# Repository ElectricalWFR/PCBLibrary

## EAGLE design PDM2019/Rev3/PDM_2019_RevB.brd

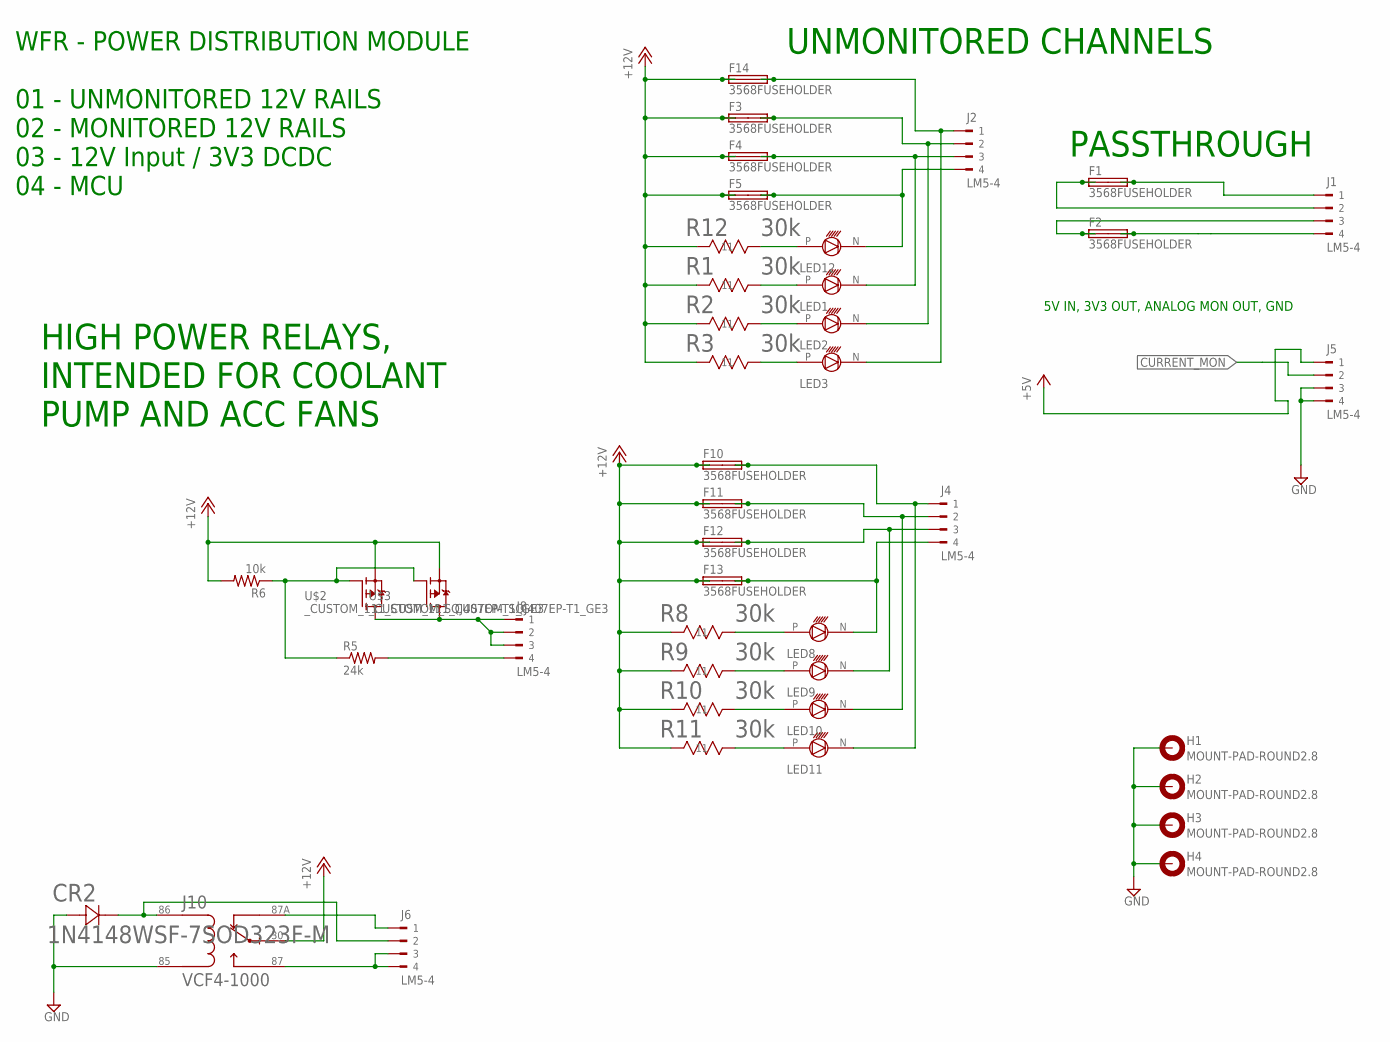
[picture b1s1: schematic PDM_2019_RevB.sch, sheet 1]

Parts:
CR2: 1N4148WSF-7SOD323F-M; SOD323F-M
F1, F2, F3, F4, F5, F10, F11, F12, F13, F14: 3568FUSEHOLDER; 3568
H1, H2, H3, H4: MOUNT-PAD-ROUND2.8; 2,8-PAD
J1, J2, J4, J5, J6, J8: LM5-4; 281-1423
J10: VCF4-1000; TE_VCF4-1000
LED1, LED2, LED3, LED8, LED9, LED10, LED11, LED12: 5MM_LED
R1, R2, R3, R8, R9, R10, R11, R12: 30k; STA_RMCF0805
R5: 24k; M0805
R6: 10k; M0805
U$2, U$3: _CUSTOM_111_CUSTOM_SQJ407EP-T1_GE3; _CUSTOM_111_CUSTOM_TRANS_SIRA90DP-T1-GE3

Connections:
+5V: J5.P$1 (1); also elsewhere on the board
+12V: F3.L1 (1A), F3.L2 (1B), F4.L1 (1A), F4.L2 (1B), F5.L1 (1A), F5.L2 (1B), F10.L1 (1A), F10.L2 (1B), F11.L1 (1A), F11.L2 (1B), F12.L1 (1A), F12.L2 (1B), F13.L1 (1A), F13.L2 (1B), F14.L1 (1A), F14.L2 (1B), J10.30, R1.1 (11), R2.1 (11), R3.1 (11), R6.2, R8.1 (11), R9.1 (11), R10.1 (11), R11.1 (11), R12.1 (11), U$2.1 (S), U$2.2 (S), U$2.3 (S), U$3.1 (S), U$3.2 (S), U$3.3 (S); also elsewhere on the board
CURRENT_MON: J5.P$2 (2); also elsewhere on the board
GND: CR2.2 (21), H1.B2,8, H2.B2,8, H3.B2,8, H4.B2,8, J5.P$3 (3), J5.P$4 (4), J10.85; also elsewhere on the board
unnamed: F1.R1 (2A), F1.R2 (2B), J1.P$1 (1)
unnamed: F1.L1 (1A), F1.L2 (1B), J1.P$2 (2)
unnamed: F2.L1 (1A), F2.L2 (1B), J1.P$3 (3)
unnamed: LED11.P, R11.2 (22)
unnamed: LED12.P, R12.2 (22)
unnamed: F4.R1 (2A), F4.R2 (2B), J2.P$3 (3), LED1.N
unnamed: F5.R1 (2A), F5.R2 (2B), J2.P$4 (4), LED12.N
unnamed: J8.P$4 (4), R5.2
unnamed: J8.P$1 (1), J8.P$2 (2), J8.P$3 (3), U$2.5 (D), U$3.5 (D)
unnamed: F10.R1 (2A), F10.R2 (2B), J4.P$1 (1), LED11.N
unnamed: F13.R1 (2A), F13.R2 (2B), J4.P$4 (4), LED8.N
unnamed: F12.R1 (2A), F12.R2 (2B), J4.P$3 (3), LED9.N
unnamed: F11.R1 (2A), F11.R2 (2B), J4.P$2 (2), LED10.N
unnamed: R5.1, R6.1, U$2.4 (G), U$3.4 (G)
unnamed: LED10.P, R10.2 (22)
unnamed: LED8.P, R8.2 (22)
unnamed: CR2.1 (12), J6.P$2 (2), J10.86
unnamed: LED9.P, R9.2 (22)
unnamed: F2.R1 (2A), F2.R2 (2B), J1.P$4 (4)
unnamed: LED1.P, R1.2 (22)
unnamed: LED2.P, R2.2 (22)
unnamed: LED3.P, R3.2 (22)
unnamed: F3.R1 (2A), F3.R2 (2B), J2.P$2 (2), LED2.N
unnamed: F14.R1 (2A), F14.R2 (2B), J2.P$1 (1), LED3.N
unnamed: J6.P$3 (3), J6.P$4 (4), J10.87
unnamed: J6.P$1 (1), J10.87A

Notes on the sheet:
WFR - POWER DISTRIBUTION MODULE 01 - UNMONITORED 12V RAILS 02 - MONITORED 12V RAILS 03 - 12V Input / 3V3 DCDC 04 - MCU
HIGH POWER RELAYS, INTENDED FOR COOLANT PUMP AND ACC FANS
UNMONITORED CHANNELS
PASSTHROUGH
5V IN, 3V3 OUT, ANALOG MON OUT, GND

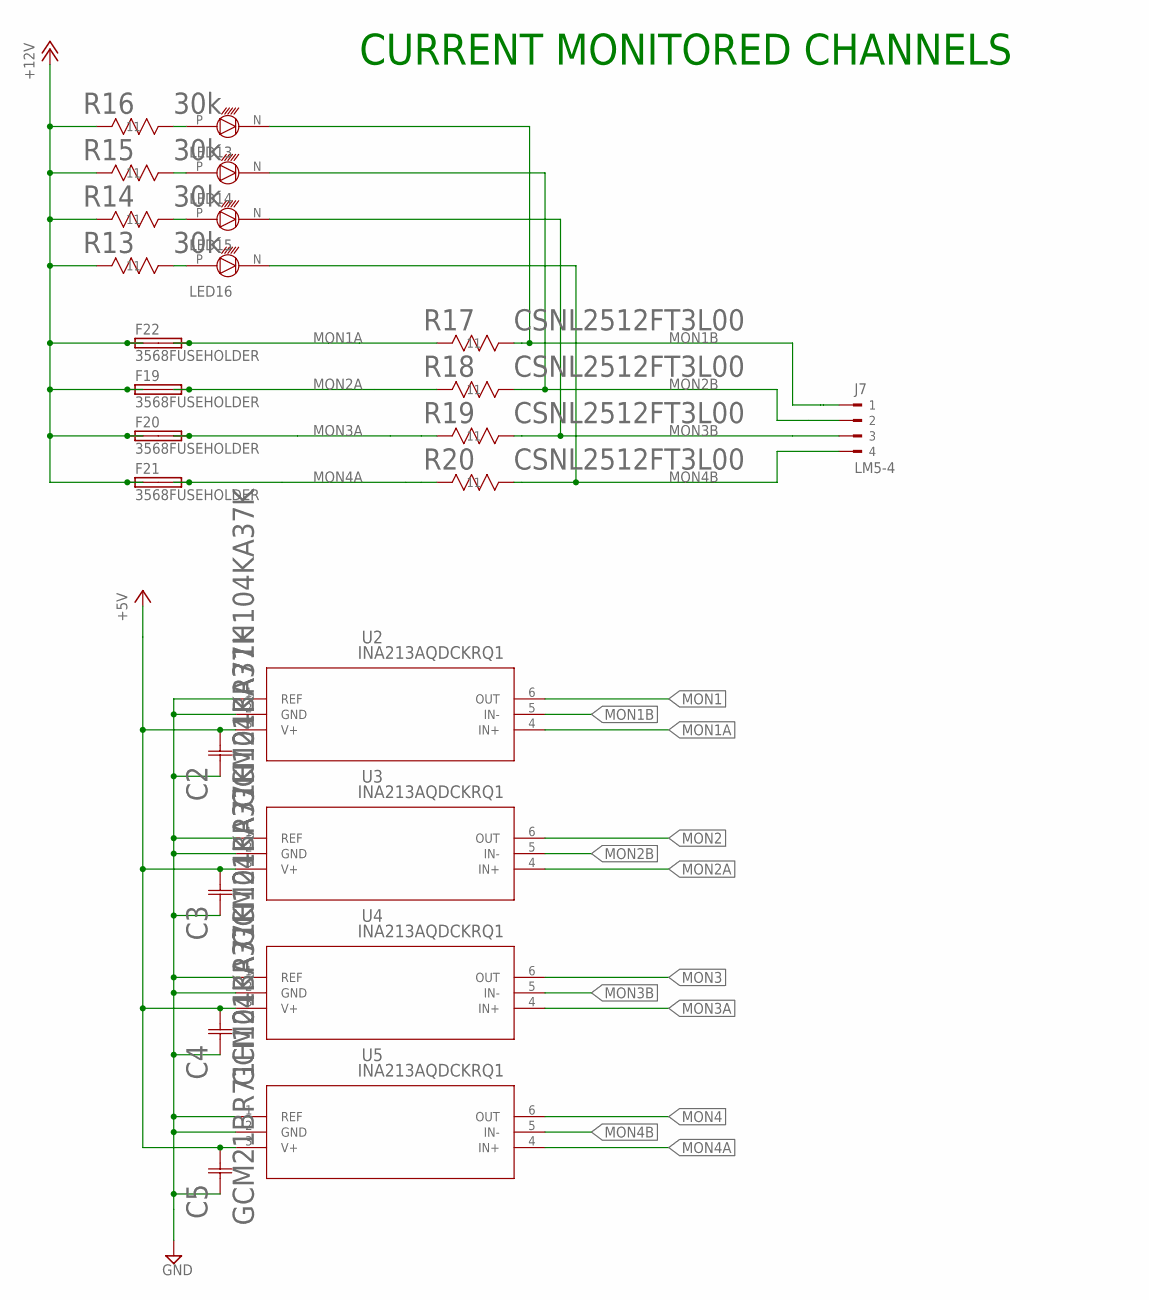
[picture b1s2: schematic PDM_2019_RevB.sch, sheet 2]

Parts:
C2, C3, C4, C5: GCM21BR71H104KA37K; G-21
F19, F20, F21, F22: 3568FUSEHOLDER; 3568
J7: LM5-4; 281-1423
LED13, LED14, LED15, LED16: 5MM_LED
R13, R14, R15, R16: 30k; STA_RMCF0805
R17, R18, R19, R20: CSNL2512FT3L00; STA_CSNL2512(3)
U2, U3, U4, U5: INA213AQDCKRQ1; DCK6

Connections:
+5V: C2.2 (22), C3.2 (22), C4.2 (22), C5.2 (22), U2.3 (V+), U3.3 (V+), U4.3 (V+), U5.3 (V+); also elsewhere on the board
+12V: F19.L1 (1A), F19.L2 (1B), F20.L1 (1A), F20.L2 (1B), F21.L1 (1A), F21.L2 (1B), F22.L1 (1A), F22.L2 (1B), R13.1 (11), R14.1 (11), R15.1 (11), R16.1 (11); also elsewhere on the board
GND: C2.1 (11), C3.1 (11), C4.1 (11), C5.1 (11), U2.1 (REF), U2.2 (GND), U3.1 (REF), U3.2 (GND), U4.1 (REF), U4.2 (GND), U5.1 (REF), U5.2 (GND); also elsewhere on the board
MON1: U2.6 (OUT); also elsewhere on the board
MON1A: F22.R1 (2A), F22.R2 (2B), R17.1 (11), U2.4 (IN+)
MON1B: J7.P$1 (1), LED13.N, R17.2 (22), U2.5 (IN-)
MON2: U3.6 (OUT); also elsewhere on the board
MON2A: F19.R1 (2A), F19.R2 (2B), R18.1 (11), U3.4 (IN+)
MON2B: J7.P$2 (2), LED14.N, R18.2 (22), U3.5 (IN-)
MON3: U4.6 (OUT); also elsewhere on the board
MON3A: F20.R1 (2A), F20.R2 (2B), R19.1 (11), U4.4 (IN+)
MON3B: J7.P$3 (3), LED15.N, R19.2 (22), U4.5 (IN-)
MON4: U5.6 (OUT); also elsewhere on the board
MON4A: F21.R1 (2A), F21.R2 (2B), R20.1 (11), U5.4 (IN+)
MON4B: J7.P$4 (4), LED16.N, R20.2 (22), U5.5 (IN-)
unnamed: LED16.P, R13.2 (22)
unnamed: LED15.P, R14.2 (22)
unnamed: LED14.P, R15.2 (22)
unnamed: LED13.P, R16.2 (22)

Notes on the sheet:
CURRENT MONITORED CHANNELS

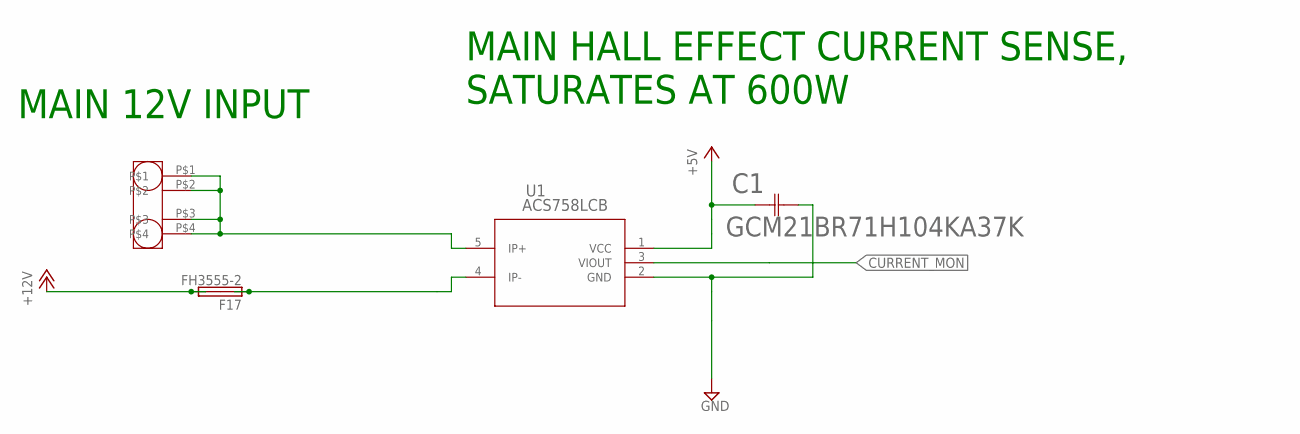
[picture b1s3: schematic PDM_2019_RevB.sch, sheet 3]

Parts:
C1: GCM21BR71H104KA37K; G-21
F17: FH3555-2; 3555-2
U1: ACS758LCB; PFF-5
U$1: 1773976

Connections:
+5V: C1.1 (11), U1.1 (VCC); also elsewhere on the board
+12V: F17.R1 (2A), F17.R2 (2B); also elsewhere on the board
CURRENT_MON: U1.3 (VIOUT); also elsewhere on the board
GND: C1.2 (22), U1.2 (GND); also elsewhere on the board
unnamed: U1.5 (IP+), U$1.P$1, U$1.P$2, U$1.P$3, U$1.P$4
unnamed: F17.L1 (1A), F17.L2 (1B), U1.4 (IP-)

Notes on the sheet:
MAIN 12V INPUT
MAIN HALL EFFECT CURRENT SENSE, SATURATES AT 600W

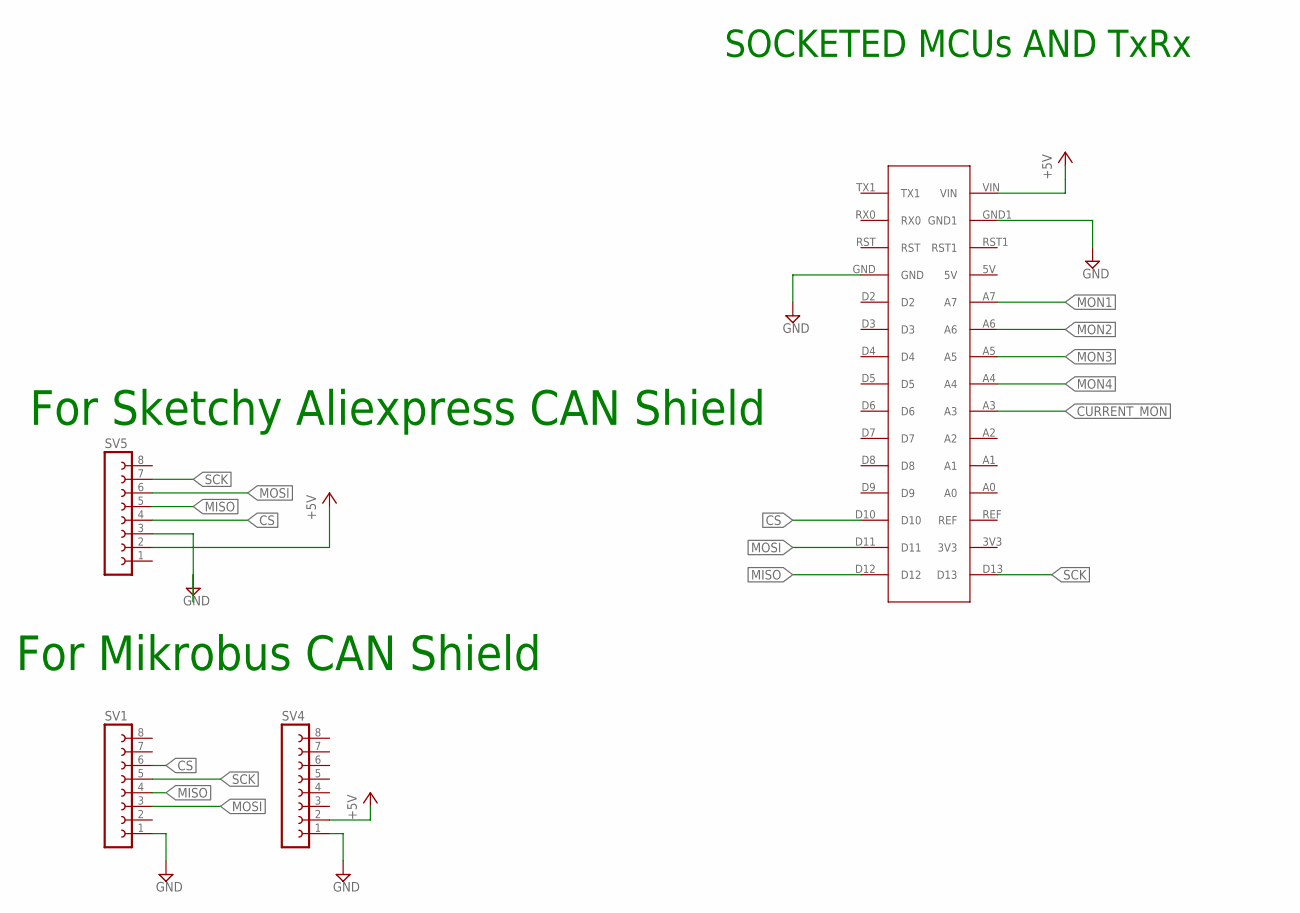
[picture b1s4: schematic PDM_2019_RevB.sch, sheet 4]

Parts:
SV1, SV4, SV5: FE08-1; FE08
U$4: NANO

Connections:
+5V: SV4.2; also elsewhere on the board
CS: SV1.6, SV5.4, U$4.D10
CURRENT_MON: U$4.A3; also elsewhere on the board
GND: SV1.1, SV4.1, U$4.GND, U$4.GND1; also elsewhere on the board
MISO: SV1.4, SV5.5, U$4.D12
MON1: U$4.A7; also elsewhere on the board
MON2: U$4.A6; also elsewhere on the board
MON3: U$4.A5; also elsewhere on the board
MON4: U$4.A4; also elsewhere on the board
MOSI: SV1.3, SV5.6, U$4.D11
SCK: SV1.5, SV5.7, U$4.D13

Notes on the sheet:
For Mikrobus CAN Shield
For Sketchy Aliexpress CAN Shield
SOCKETED MCUs AND TxRx

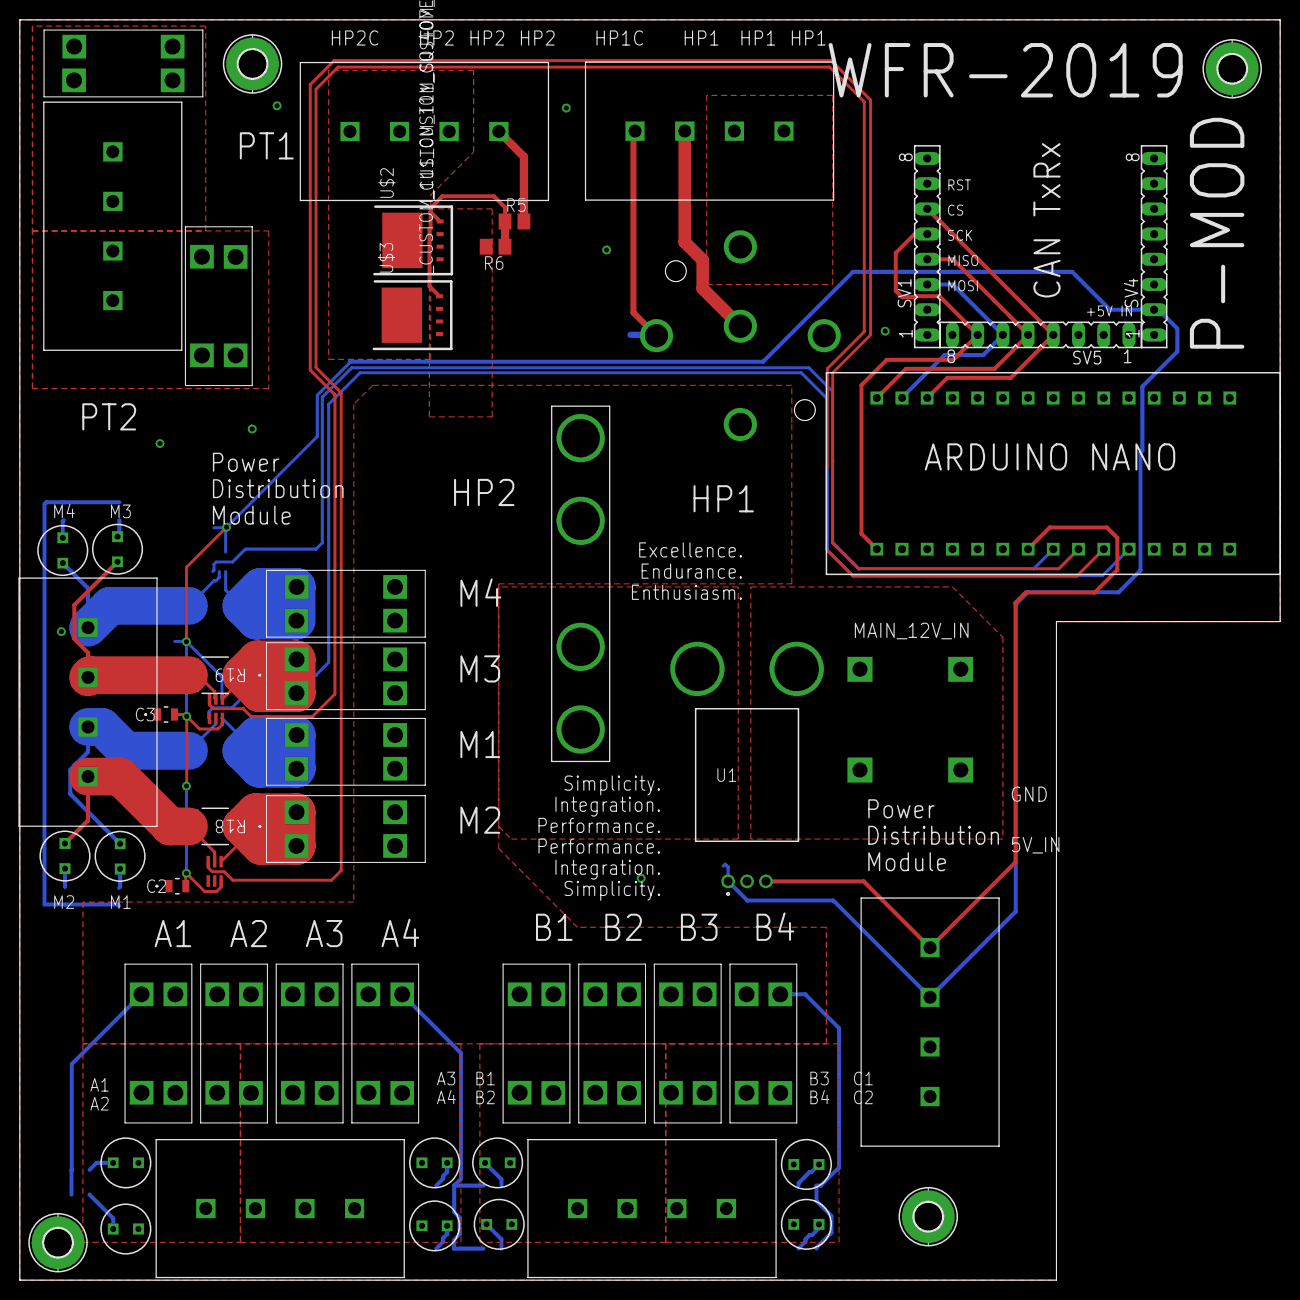
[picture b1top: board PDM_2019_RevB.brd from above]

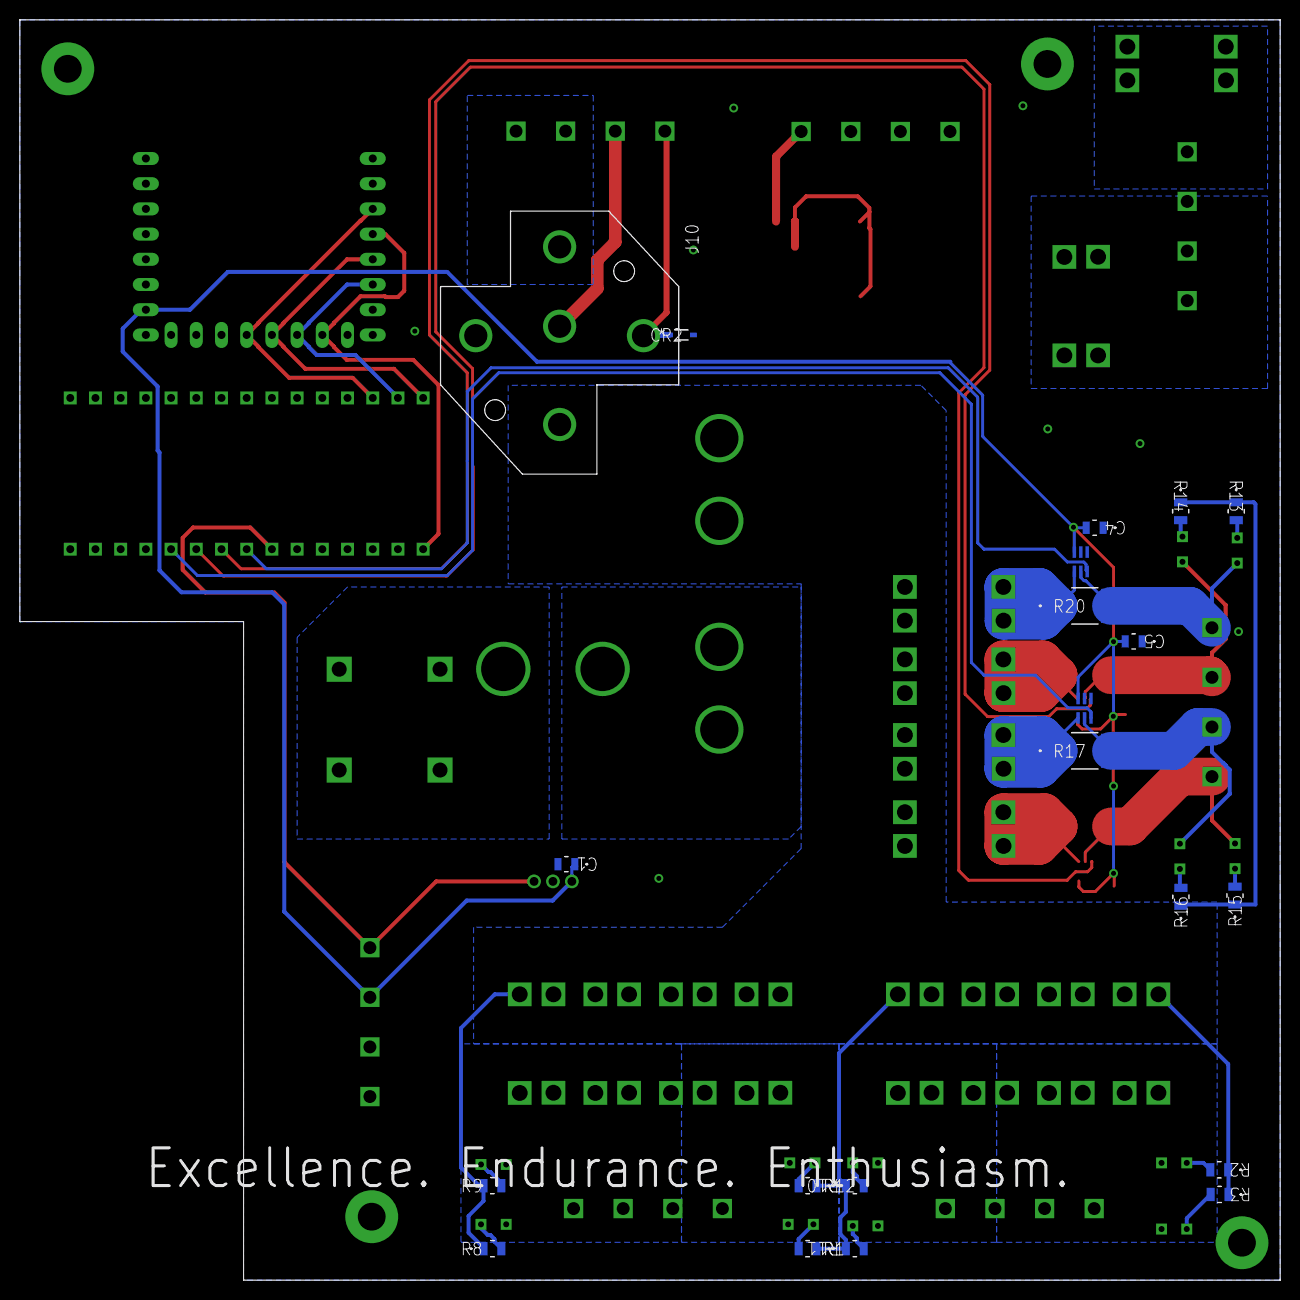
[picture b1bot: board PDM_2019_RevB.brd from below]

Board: 2 copper layers, 127.0 x 127.0 mm, 75 parts (21 on the bottom side), 52 nets.

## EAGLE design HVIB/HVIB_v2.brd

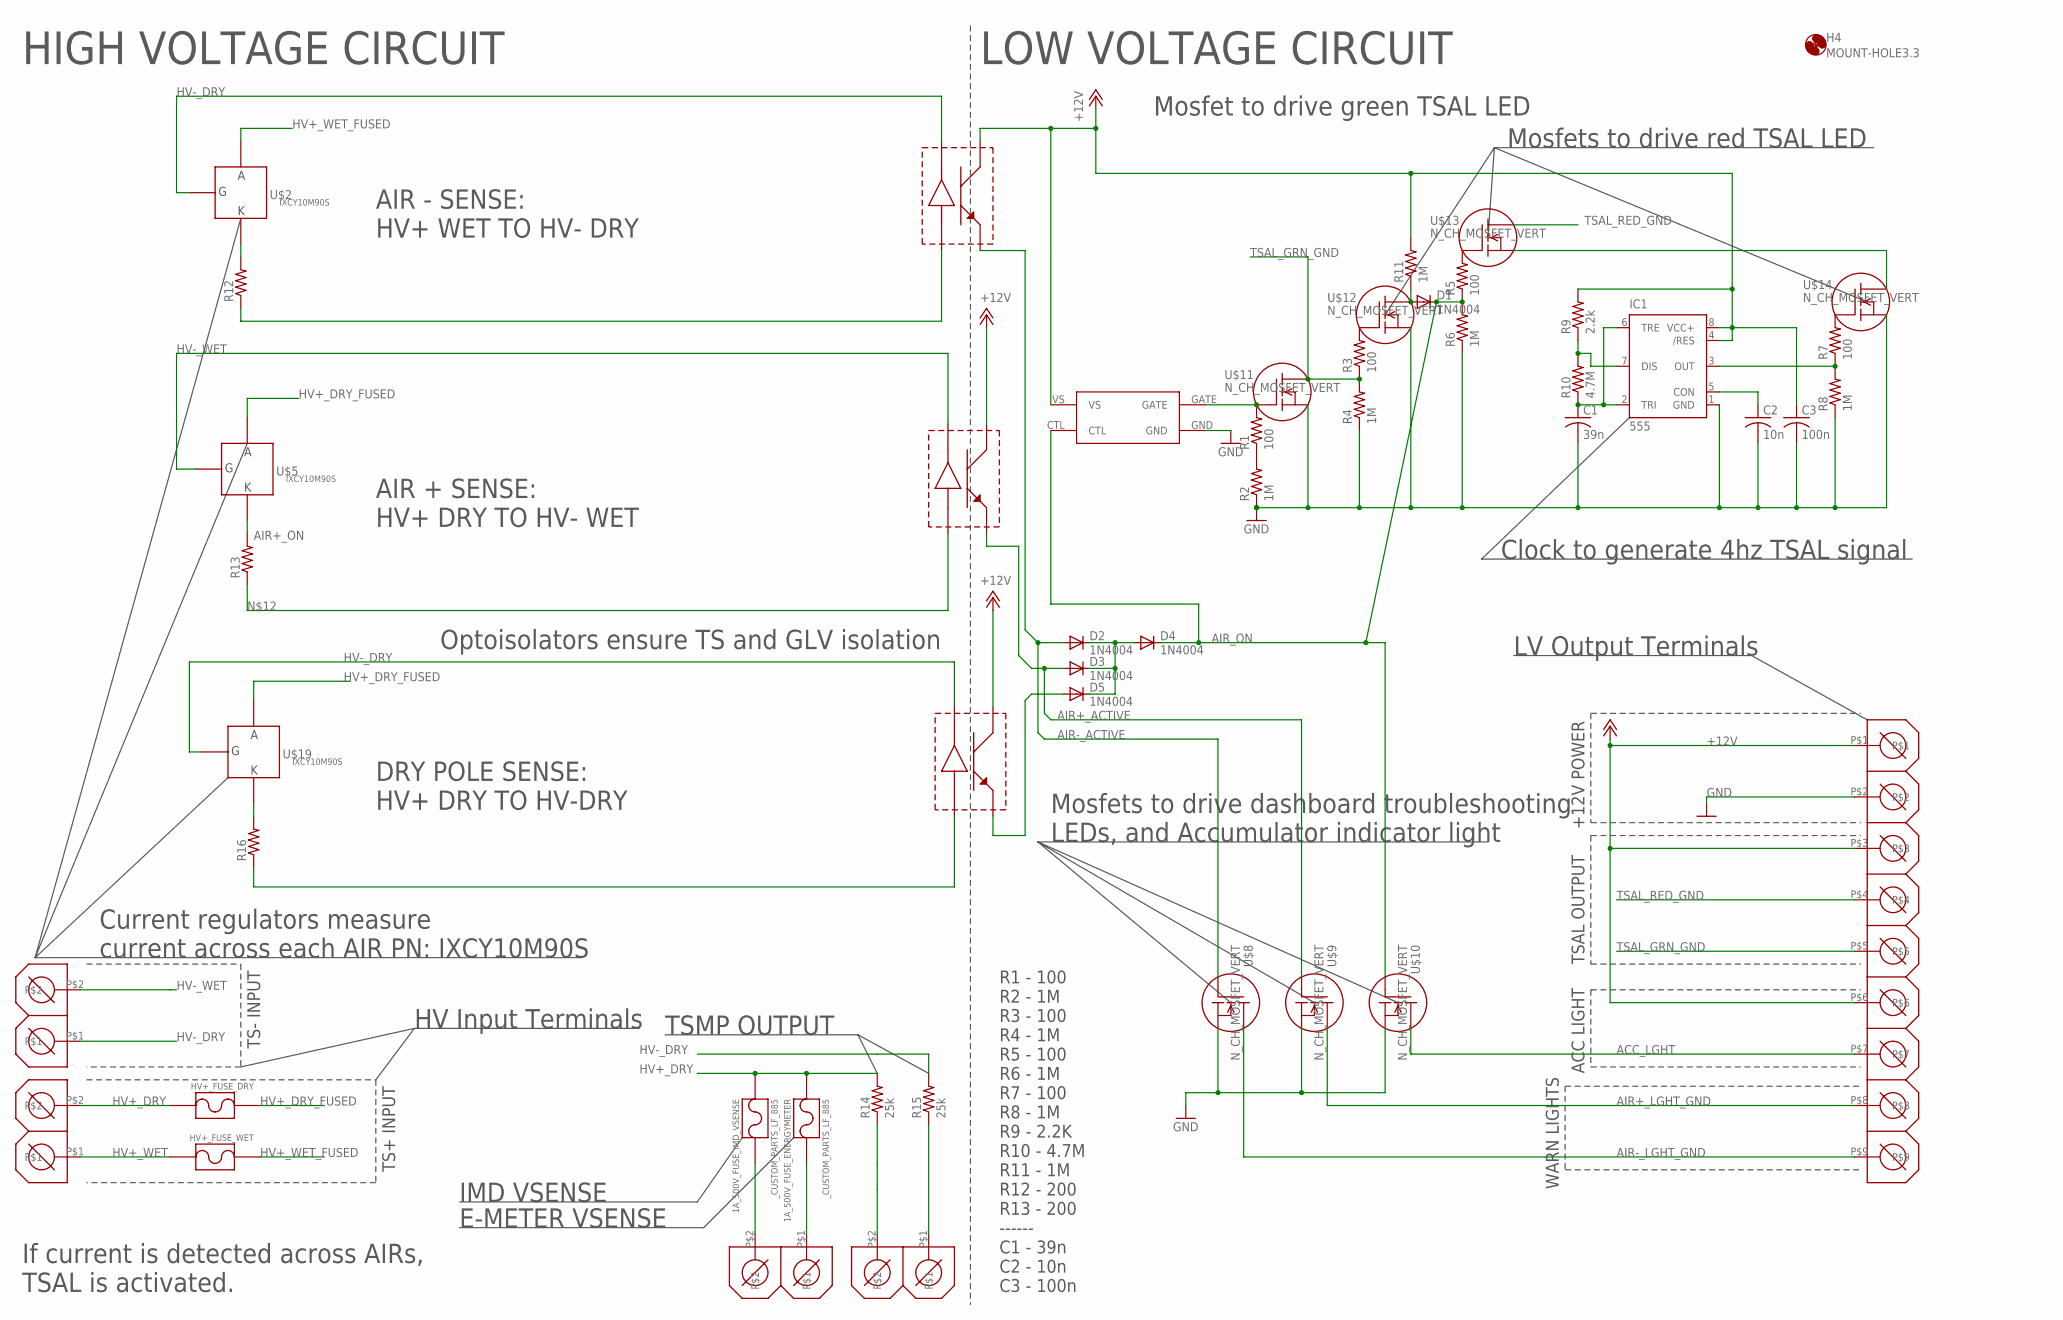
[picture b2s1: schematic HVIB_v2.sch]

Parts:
1A_500V_FUSE_ENERGYMETER, 1A_500V_FUSE_IMD_VSENSE: _CUSTOM_PARTS_LF_885
C1: 39n; C025-024X044
C2: 10n; C025-024X044
C3: 100n; C0603
D1, D2, D3, D4, D5: 1N4004; DO41-10
H4: MOUNT-HOLE3.3; 3,3
HV+_FUSE_DRY: _CUSTOM_PARTS_LF_885
HV+_FUSE_WET: _CUSTOM_PARTS_LF_885
IC1: 555; DIP08
R1, R3, R5, R7: 100; 0204/5
R2, R4, R6, R8, R11: 1M; 0204/5
R9: 2.2k; 0204/5
R10: 4.7M; 0204/5
R12, R13, R16: R-US_R2010; R2010
R14, R15: 25k; R2010
U$1, U$3, U$18: OPI7002; DIL04
U$2, U$5, U$19: IXCY10M90S; D2PACK
U$4, U$6, U$16, U$17: DCDC_PARTS_282838-2_TE; DCDC_PARTS_282838-2_FOOT
U$7: PHOENIX_1725724; 1725724_FOOT
U$8, U$9, U$10, U$11, U$12, U$13, U$14: N_CH_MOSFET_VERT; TO220V
U$15: MIC4417; PDM_2019_REVB_MIC4416YM4-TR

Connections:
+12V: C3.1, IC1.4 (/RES), IC1.8 (VCC+), R9.2, R11.2, U$1.3 (COLLECTOR), U$3.3 (COLLECTOR), U$7.P$1, U$7.P$3, U$7.P$6, U$15.VS, U$18.3 (COLLECTOR)
ACC_LGHT: U$7.P$7, U$10.2 (D)
AIR+_ACTIVE: D3.A, U$1.4 (EMITTER), U$9.1 (G)
AIR+_LGHT_GND: U$7.P$8, U$9.2 (D)
AIR+_ON: R13.2, U$5.3 (K)
AIR-_ACTIVE: D2.A, U$3.4 (EMITTER), U$8.1 (G)
AIR-_LGHT_GND: U$7.P$9, U$8.2 (D)
AIR-_ON: R12.2, U$2.3 (K)
AIR_ON: D1.C, D4.C, R5.1, R6.2, U$10.1 (G), U$15.CTL
GND: C1.2, C2.2, C3.2, IC1.1 (GND), R2.1, R4.1, R6.1, R8.1, U$7.P$2, U$8.3 (S), U$9.3 (S), U$10.3 (S), U$11.3 (S), U$12.3 (S), U$14.3 (S), U$15.GND
HV+_DRY: 1A_500V_FUSE_ENERGYMETER.P$1, 1A_500V_FUSE_IMD_VSENSE.P$1, HV+_FUSE_DRY.P$2, R14.2, U$6.P$2
HV+_DRY_FUSED: HV+_FUSE_DRY.P$1, U$5.2 (A), U$19.2 (A)
HV+_WET: HV+_FUSE_WET.P$2, U$6.P$1
HV+_WET_FUSED: HV+_FUSE_WET.P$1, U$2.2 (A)
HV-_DRY: R15.2, U$2.1 (G), U$3.2 (CATHODE), U$4.P$1, U$18.2 (CATHODE), U$19.1 (G)
HV-_WET: U$1.2 (CATHODE), U$4.P$2, U$5.1 (G)
unnamed: R1.1, R2.2
unnamed: R1.2, U$11.1 (G), U$15.GATE
unnamed: R3.2, U$12.1 (G)
unnamed: C2.1, IC1.5 (CON)
unnamed: IC1.7 (DIS), R9.1, R10.2
unnamed: R5.2, U$13.1 (G)
unnamed: R7.2, U$14.1 (G)
unnamed: IC1.3 (OUT), R7.1, R8.2
unnamed: C1.1, IC1.2 (TRI), IC1.6 (TRE), R10.1
unnamed: R12.1, U$3.1 (ANODE)
unnamed: R13.1, U$1.1 (ANODE)
unnamed: U$13.3 (S), U$14.2 (D)
unnamed: D2.C, D3.C, D4.A, D5.C
unnamed: D1.A, R11.1, U$12.2 (D)
unnamed: R16.2, U$19.3 (K)
unnamed: R14.1, U$16.P$2
unnamed: 1A_500V_FUSE_IMD_VSENSE.P$2, U$17.P$2
unnamed: 1A_500V_FUSE_ENERGYMETER.P$2, U$17.P$1
unnamed: R15.1, U$16.P$1
unnamed: R16.1, U$18.1 (ANODE)
unnamed: D5.A, U$18.4 (EMITTER)
TSAL_GRN_GND: R3.1, R4.2, U$7.P$5, U$11.2 (D)
TSAL_RED_GND: U$7.P$4, U$13.2 (D)

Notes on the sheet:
HIGH VOLTAGE CIRCUIT
LOW VOLTAGE CIRCUIT
TSAL OUTPUT
ACC LIGHT
WARN LIGHTS
Current regulators measure current across each AIR PN: IXCY10M90S
Optoisolators ensure TS and GLV isolation
Mosfets to drive dashboard troubleshooting LEDs, and Accumulator indicator light
Clock to generate 4hz TSAL signal
Mosfets to drive red TSAL LED
Mosfet to drive green TSAL LED
+12V POWER
TS- INPUT
TS+ INPUT
If current is detected across AIRs, TSAL is activated.
HV Input Terminals
LV Output Terminals
R1 - 100 R2 - 1M R3 - 100 R4 - 1M R5 - 100 R6 - 1M R7 - 100 R8 - 1M R9 - 2.2K R10 - 4.7M R11 - 1M R12 - 200 R13 - 200 ------ C1 - 39n C2 - 10n C3 - 100n
TSMP OUTPUT
E-METER VSENSE
IMD VSENSE
AIR - SENSE: HV+ WET TO HV- DRY
AIR + SENSE: HV+ DRY TO HV- WET
DRY POLE SENSE: HV+ DRY TO HV-DRY

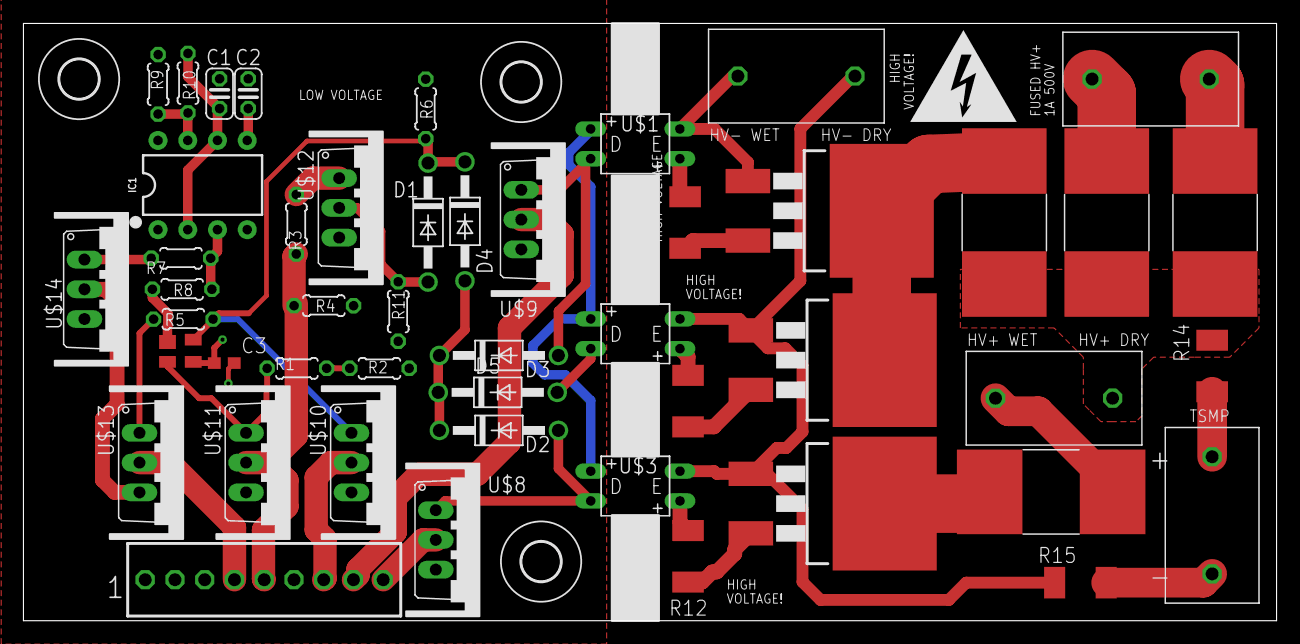
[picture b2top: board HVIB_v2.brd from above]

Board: 2 copper layers, 107.0 x 51.0 mm, 51 parts (0 on the bottom side), 39 nets.

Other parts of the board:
H1, H2: MOUNT-HOLE3.3; 3,3

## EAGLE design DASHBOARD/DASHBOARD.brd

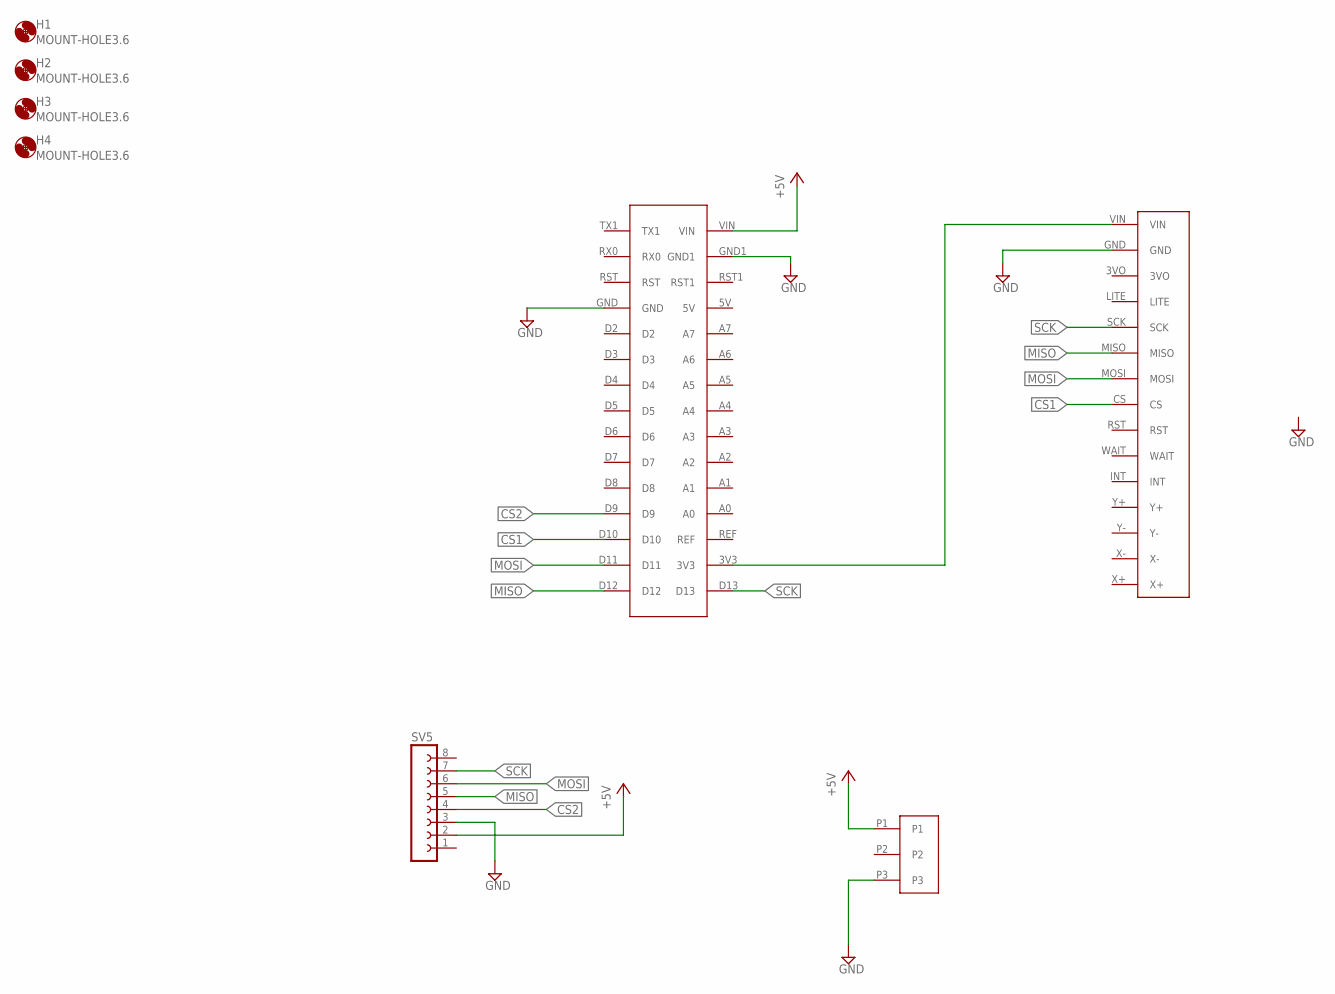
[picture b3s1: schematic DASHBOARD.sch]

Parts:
H1, H2, H3, H4: MOUNT-HOLE3.6; 3,6
SV5: FE08-1; FE08
U$1: BREAKOUT
U$2: NANO
U$3: 1935789

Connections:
CS1: U$1.CS, U$2.D10
CS2: SV5.4, U$2.D9
GND: SV5.3, U$1.GND, U$2.GND, U$2.GND1, U$3.P3
MISO: SV5.5, U$1.MISO, U$2.D12
MOSI: SV5.6, U$1.MOSI, U$2.D11
unnamed: U$1.VIN, U$2.3V3
unnamed: SV5.2, U$2.VIN, U$3.P1
SCK: SV5.7, U$1.SCK, U$2.D13

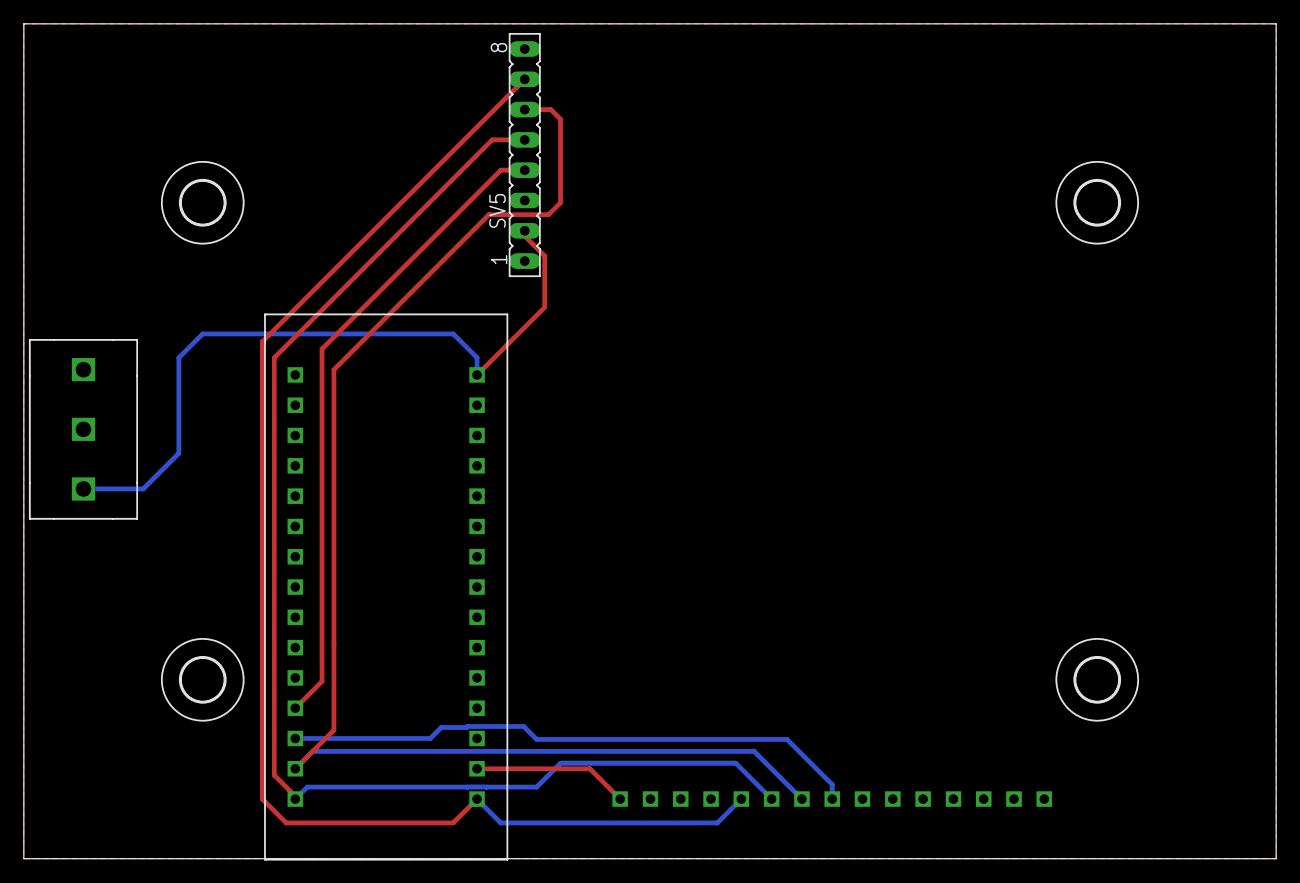
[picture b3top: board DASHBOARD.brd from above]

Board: 2 copper layers, 105.0 x 70.0 mm, 8 parts (0 on the bottom side), 8 nets.

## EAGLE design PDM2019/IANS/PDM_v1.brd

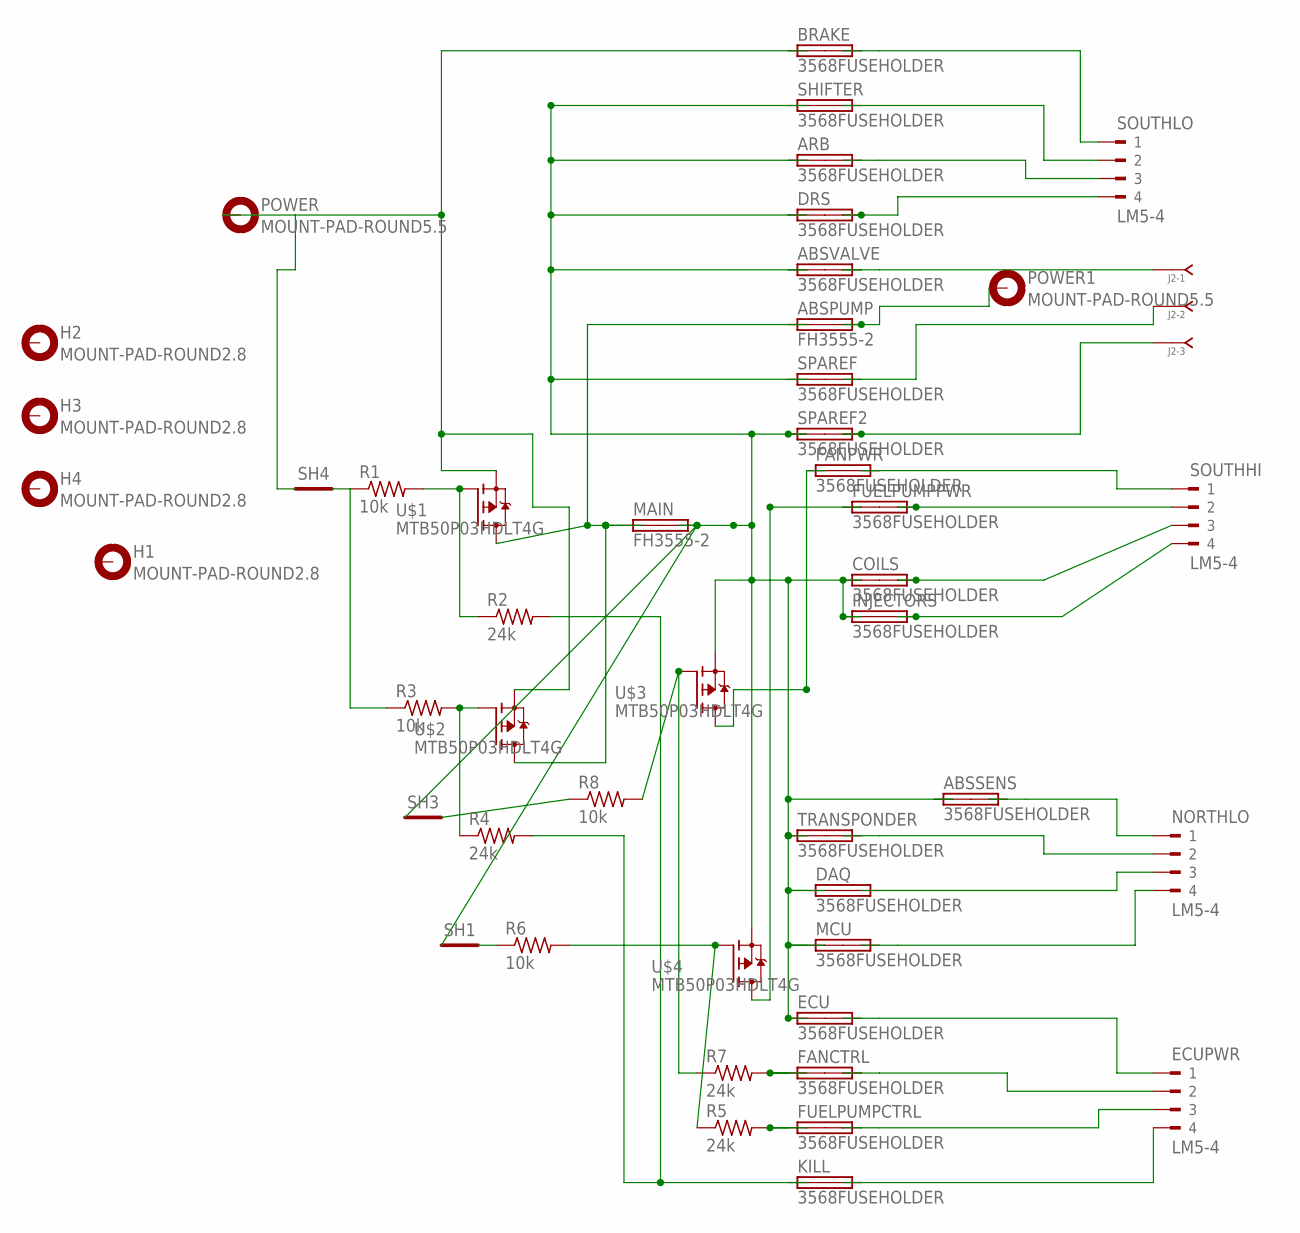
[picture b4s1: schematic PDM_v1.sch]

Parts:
ABSPUMP: FH3555-2; 3555-2
ABSSENS: 3568FUSEHOLDER; 3568
ABSVALVE: 3568FUSEHOLDER; 3568
ARB: 3568FUSEHOLDER; 3568
BRAKE: 3568FUSEHOLDER; 3568
COILS: 3568FUSEHOLDER; 3568
DAQ: 3568FUSEHOLDER; 3568
DRS: 3568FUSEHOLDER; 3568
ECU: 3568FUSEHOLDER; 3568
ECUPWR: LM5-4; 281-1423
FANCTRL: 3568FUSEHOLDER; 3568
FANPWR: 3568FUSEHOLDER; 3568
FUELPUMPCTRL: 3568FUSEHOLDER; 3568
FUELPUMPPWR: 3568FUSEHOLDER; 3568
H1, H2, H3, H4: MOUNT-PAD-ROUND2.8; 2,8-PAD
INJECTORS: 3568FUSEHOLDER; 3568
J2: J-04-; 535512-04
KILL: 3568FUSEHOLDER; 3568
MAIN: FH3555-2; 3555-2
MCU: 3568FUSEHOLDER; 3568
NORTHLO: LM5-4; 281-1423
POWER, POWER1: MOUNT-PAD-ROUND5.5; 5,5-PAD
R1, R3, R6, R8: 10k; M0805
R2, R4, R5, R7: 24k; M0805
SH1, SH3, SH4: SHORTA5; SHORT_ALL-50
SHIFTER: 3568FUSEHOLDER; 3568
SOUTHHI: LM5-4; 281-1423
SOUTHLO: LM5-4; 281-1423
SPAREF, SPAREF2: 3568FUSEHOLDER; 3568
TRANSPONDER: 3568FUSEHOLDER; 3568
U$1, U$2, U$3, U$4: MTB50P03HDLT4G; TO263

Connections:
+12V: BRAKE.L1 (1A), BRAKE.L2 (1B), POWER.B5,5, SH4.1, U$1.2 (S), U$2.2 (S)
MAINRAIL: ABSSENS.L1 (1A), ABSSENS.L2 (1B), ABSVALVE.L1 (1A), ABSVALVE.L2 (1B), ARB.L1 (1A), ARB.L2 (1B), COILS.L1 (1A), COILS.L2 (1B), DAQ.L1 (1A), DAQ.L2 (1B), DRS.L1 (1A), DRS.L2 (1B), ECU.L1 (1A), ECU.L2 (1B), INJECTORS.L1 (1A), INJECTORS.L2 (1B), MAIN.R1 (2A), MAIN.R2 (2B), MCU.L1 (1A), MCU.L2 (1B), SH1.1, SH3.1, SHIFTER.L1 (1A), SHIFTER.L2 (1B), SPAREF.L1 (1A), SPAREF.L2 (1B), SPAREF2.L1 (1A), SPAREF2.L2 (1B), TRANSPONDER.L1 (1A), TRANSPONDER.L2 (1B), U$3.2 (S), U$4.2 (S)
unnamed: INJECTORS.R1 (2A), INJECTORS.R2 (2B), SOUTHHI.P$4 (4)
unnamed: ABSPUMP.L1 (1A), ABSPUMP.L2 (1B), MAIN.L1 (1A), MAIN.L2 (1B), U$1.3 (D), U$2.3 (D)
unnamed: R3.2, R4.1, U$2.1 (G)
unnamed: FUELPUMPPWR.R1 (2A), FUELPUMPPWR.R2 (2B), SOUTHHI.P$2 (2)
unnamed: KILL.L1 (1A), KILL.L2 (1B), R2.2, R4.2
unnamed: ECU.R1 (2A), ECU.R2 (2B), ECUPWR.P$1 (1)
unnamed: ABSPUMP.R1 (2A), ABSPUMP.R2 (2B), POWER1.B5,5
unnamed: ECUPWR.P$2 (2), FANCTRL.R1 (2A), FANCTRL.R2 (2B)
unnamed: ABSVALVE.R1 (2A), ABSVALVE.R2 (2B), J2.LEFT
unnamed: BRAKE.R1 (2A), BRAKE.R2 (2B), SOUTHLO.P$1 (1)
unnamed: FANCTRL.L1 (1A), FANCTRL.L2 (1B), R7.2
unnamed: SHIFTER.R1 (2A), SHIFTER.R2 (2B), SOUTHLO.P$2 (2)
unnamed: COILS.R1 (2A), COILS.R2 (2B), SOUTHHI.P$3 (3)
unnamed: ABSSENS.R1 (2A), ABSSENS.R2 (2B), NORTHLO.P$1 (1)
unnamed: NORTHLO.P$2 (2), TRANSPONDER.R1 (2A), TRANSPONDER.R2 (2B)
unnamed: DAQ.R1 (2A), DAQ.R2 (2B), NORTHLO.P$3 (3)
unnamed: MCU.R1 (2A), MCU.R2 (2B), NORTHLO.P$4 (4)
unnamed: ECUPWR.P$3 (3), FUELPUMPCTRL.R1 (2A), FUELPUMPCTRL.R2 (2B)
unnamed: ECUPWR.P$4 (4), KILL.R1 (2A), KILL.R2 (2B)
unnamed: ARB.R1 (2A), ARB.R2 (2B), SOUTHLO.P$3 (3)
unnamed: DRS.R1 (2A), DRS.R2 (2B), SOUTHLO.P$4 (4)
unnamed: R1.2, R2.1, U$1.1 (G)
unnamed: R5.1, R6.2, U$4.1 (G)
unnamed: J2.MIDDLE, SPAREF.R1 (2A), SPAREF.R2 (2B)
unnamed: J2.RIGHT, SPAREF2.R1 (2A), SPAREF2.R2 (2B)
unnamed: FUELPUMPPWR.L1 (1A), FUELPUMPPWR.L2 (1B), U$4.3 (D)
unnamed: FANPWR.R1 (2A), FANPWR.R2 (2B), SOUTHHI.P$1 (1)
unnamed: R7.1, R8.2, U$3.1 (G)
unnamed: FUELPUMPCTRL.L1 (1A), FUELPUMPCTRL.L2 (1B), R5.2
unnamed: R1.1, R3.1, SH4.2
unnamed: R8.1, SH3.2
unnamed: FANPWR.L1 (1A), FANPWR.L2 (1B), U$3.3 (D)
unnamed: R6.1, SH1.2

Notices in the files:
parts and their libraries:
SparkFun-IC-Special-Function: Licensing: Creative Commons ShareAlike 4.0 International - https://creativecommons.org/licenses/by-sa/4.0
